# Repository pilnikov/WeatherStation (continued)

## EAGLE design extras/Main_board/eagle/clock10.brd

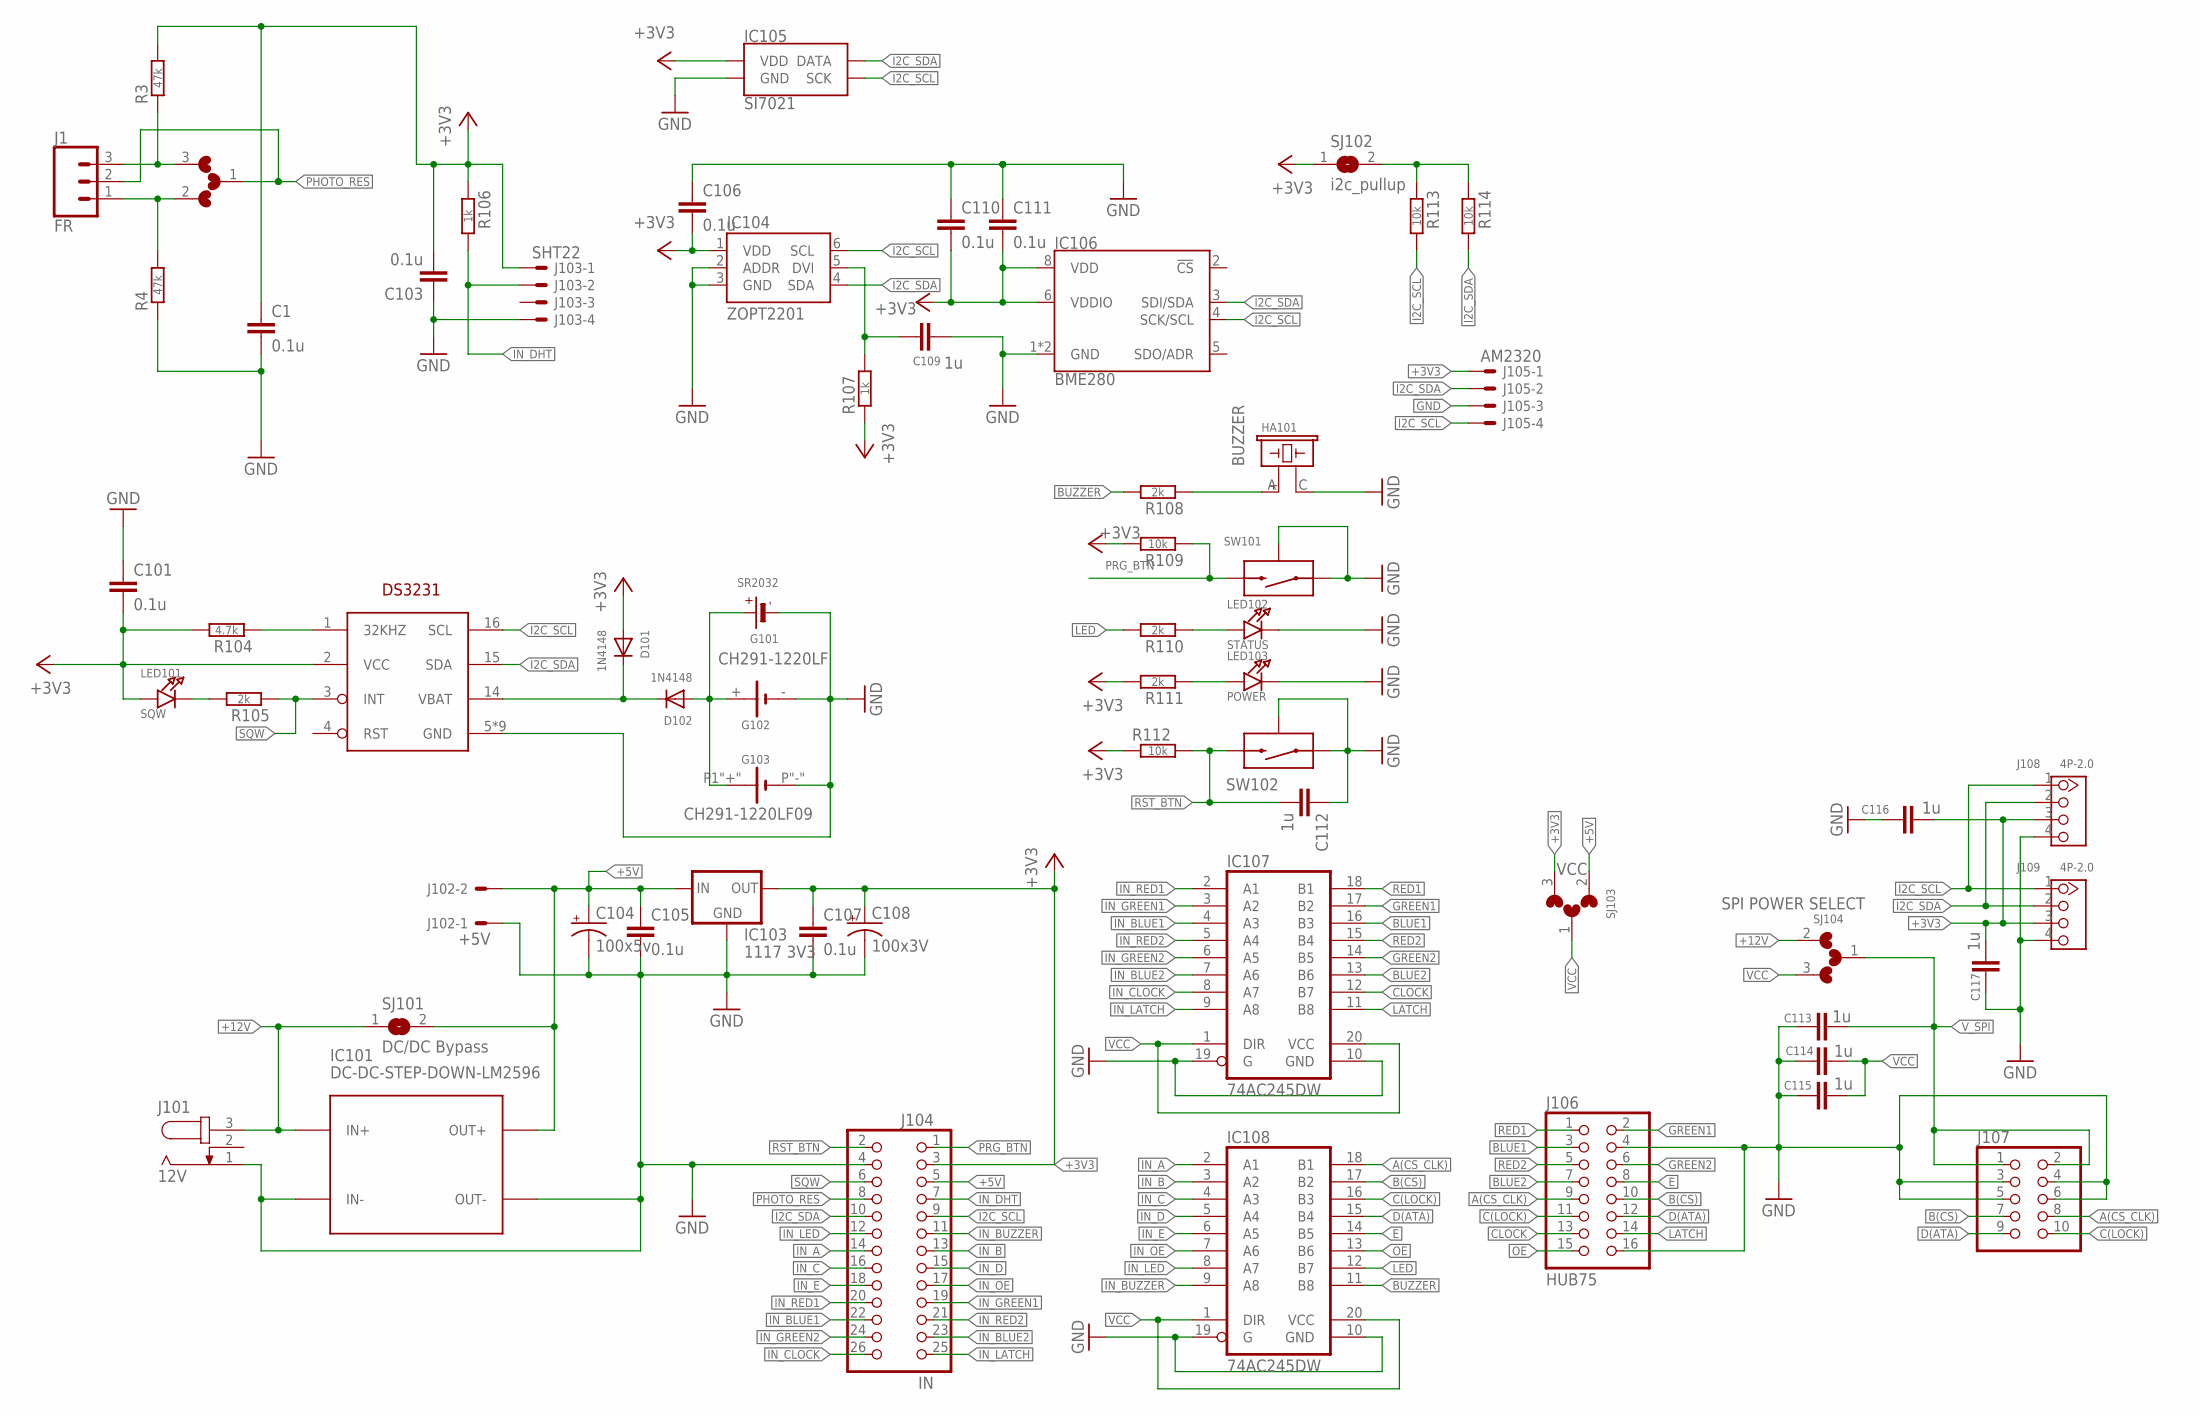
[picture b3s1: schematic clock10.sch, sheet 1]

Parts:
C1, C101, C103, C105, C106, C107, C110, C111: 0.1u; 0603-CAP
C104: 100x5v; CPOL-RADIAL-100UF-25V
C108: 100x3V; CPOL-RADIAL-100UF-25V
C109, C112, C113, C114, C115, C116, C117: 1u; 0603-CAP
D101, D102: 1N4148; SOD-323F
G101: SR2032; CR2032
G102: CH291-1220LF
G103: CH291-1220LF09; CH23-09LF
HA101: BUZZER; PBUZ_12X7.5
IC101: DC-DC-STEP-DOWN-LM2596
IC102: DS3231W; SO16W
IC103: 1117 3V3; SOT223
IC104: ZOPT2201; WSOF6L
IC105: SI7021; DFN-6-3X3-SI7021
IC106: BME280; LGA-8-2.5X2.5
IC107, IC108: 74AC245DW; SO20W
J1: FR; 1X03
J101: 12V; SPC4077
J102: +5V; 70543-02
J103: SHT22; 70543-04
J104: IN; 2X13
J105: AM2320; 70543-04
J106: HUB75; 2X08
J107: HEADER-2X5IDC; 2X05_IDC
J108, J109: 4P-2.0; HW4-2.0
LED101: SQW; CHIPLED_0603
LED102: STATUS; CHIPLED_0603
LED103: POWER; CHIPLED_0603
R3, R4: 47k; R0603
R104: 4.7k; R0603
R105, R108, R110, R111: 2k; R0603
R106, R107: 1k; R0603
R109, R112, R113, R114: 10k; R0603
SJ1: PR POS/NEG; MICROBUILDER_SOLDERJUMPER_ARROW_NOPASTE_3
SJ101: DC/DC Bypass; MICROBUILDER_SOLDERJUMPER_ARROW_NOPASTE
SJ102: i2c_pullup; MICROBUILDER_SOLDERJUMPER_ARROW_NOPASTE
SJ103: VCC; MICROBUILDER_SOLDERJUMPER_ARROW_NOPASTE_3
SJ104: SPI POWER SELECT; MICROBUILDER_SOLDERJUMPER_ARROW_NOPASTE_3
SW101: PRG; MICROPUSH-BUT_TOP
SW102: RST; MICROPUSH-BUT_TOP

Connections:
+3V3: C1.1, C101.2, C103.2, C106.2, C107.1, C108.1 (+), C110.2, C111.2, C116.2, C117.2, D101.A, IC102.2 (VCC), IC103.2 (OUT), IC103.4 (OUT), IC104.1 (VDD), IC105.VDD, IC106.6 (VDDIO), IC106.8 (VDD), J103.1, J104.3, J105.1, J108.3, J109.3, LED101.A, R3.2, R104.2, R106.1, R107.1, R109.2, R111.2, R112.1, SJ102.1, SJ103.3
+5V: C104.1 (+), C105.1, IC101.OUT+, IC103.3 (IN), J102.2, J104.5, SJ101.2, SJ103.2
+12V: IC101.IN+, J101.3, SJ101.1, SJ104.2
A(CS_CLK): IC108.18 (B1), J106.9, J107.8
B(CS): IC108.17 (B2), J106.10, J107.7
BLUE1: IC107.16 (B3), J106.3
BLUE2: IC107.13 (B6), J106.7
BUZ: HA101.A, R108.1
BUZZER: IC108.11 (B8), R108.2
C(LOCK): IC108.16 (B3), J106.11, J107.10
CLOCK: IC107.12 (B7), J106.13
D(ATA): IC108.15 (B4), J106.12, J107.9
E: IC108.14 (B5), J106.8
GND: C1.2, C101.1, C103.1, C104.2 (-), C105.2, C106.1, C107.2, C108.2 (-), C109.2, C110.1, C111.1, C112.1, C113.2, C114.2, C115.2, C116.1, C117.1, G101.-, G102.-, G103.P"-" (-), HA101.C, IC101.IN-, IC101.OUT-, IC102.5 (GND), IC102.6 (GND), IC102.7 (GND), IC102.8 (GND), IC102.9 (GND), IC102.10 (GND), IC102.11 (GND), IC102.12 (GND), IC102.13 (GND), IC103.1 (GND), IC104.2 (ADDR), IC104.3 (GND), IC105.GND, IC106.1 (GND), IC106.7 (GND), IC107.10 (GND), IC107.19 (G), IC108.10 (GND), IC108.19 (G), J101.1, J102.1, J103.4, J104.4, J105.3, J106.4, J106.16, J107.3, J107.4, J107.5, J107.6, J108.4, J109.4, LED102.C, LED103.C, R4.1, SW101.A, SW101.SH0 (SH), SW102.A, SW102.SH0 (SH); also elsewhere on the board
GREEN1: IC107.17 (B2), J106.2
GREEN2: IC107.14 (B5), J106.6
I2C_SCL: IC102.16 (SCL), IC104.6 (SCL), IC105.SCK, IC106.4 (SCK/SCL), J104.9, J105.4, J108.1, J109.1, R113.2
I2C_SDA: IC102.15 (SDA), IC104.4 (SDA), IC105.DATA, IC106.3 (SDI/SDA), J104.10, J105.2, J108.2, J109.2, R114.2
IN_A: IC108.2 (A1), J104.14
IN_B: IC108.3 (A2), J104.13
IN_BLUE1: IC107.4 (A3), J104.22
IN_BLUE2: IC107.7 (A6), J104.23
IN_BUZZER: IC108.9 (A8), J104.11
IN_C: IC108.4 (A3), J104.16
IN_CLOCK: IC107.8 (A7), J104.26
IN_D: IC108.5 (A4), J104.15
IN_DHT: J103.2, J104.7, R106.2
IN_E: IC108.6 (A5), J104.18
IN_GREEN1: IC107.3 (A2), J104.19
IN_GREEN2: IC107.6 (A5), J104.24
IN_LATCH: IC107.9 (A8), J104.25
IN_LED: IC108.8 (A7), J104.12
IN_OE: IC108.7 (A6), J104.17
IN_RED1: IC107.2 (A1), J104.20
IN_RED2: IC107.5 (A4), J104.21
LATCH: IC107.11 (B8), J106.14
LED: IC108.12 (B7), R110.2
unnamed: D101.C, D102.C, IC102.14 (VBAT)
unnamed: LED103.A, R111.1
unnamed: J1.3, R3.1, SJ1.3
unnamed: LED102.A, R110.1
unnamed: LED101.C, R105.2
unnamed: J1.1, R4.2, SJ1.2
unnamed: C109.1, IC104.5 (DVI), R107.2
unnamed: IC102.1 (32KHZ), R104.1
unnamed: R113.1, R114.1, SJ102.2
unnamed: D102.A, G101.+, G102.+, G103.P1"+" (+)
OE: IC108.13 (B6), J106.15
PHOTO_RES: J1.2, J104.8, SJ1.1
PRG_BTN: J104.1, R109.1, SW101.B
RED1: IC107.18 (B1), J106.1
RED2: IC107.15 (B4), J106.5
RST_BTN: C112.2, J104.2, R112.2, SW102.B
SQW: IC102.3 (INT), J104.6, R105.1
VCC: C114.1, C115.1, IC107.1 (DIR), IC107.20 (VCC), IC108.1 (DIR), IC108.20 (VCC), SJ103.1, SJ104.3
V_SPI: C113.1, J107.1, J107.2, SJ104.1

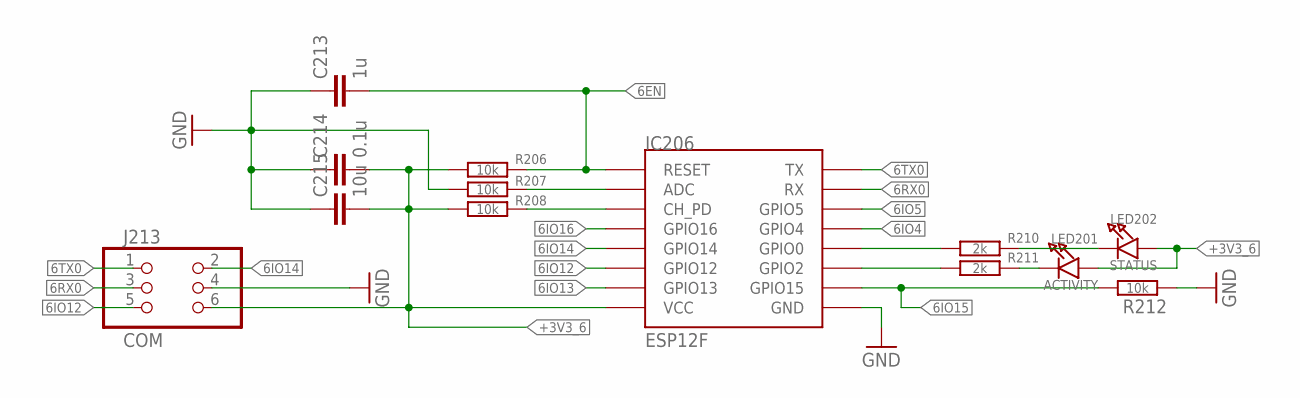
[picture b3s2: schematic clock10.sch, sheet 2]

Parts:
C213: 1u; 0603-CAP
C214: 0.1u; 0603-CAP
C215: 10u; 0603-CAP
IC206: ESP12F; ESP12-SMD
J213: COM; 2X03_SMT
LED201: ACTIVITY; CHIPLED_0603
LED202: STATUS; CHIPLED_0603
R206, R207, R208, R212: 10k; R0603
R210, R211: 2k; R0603

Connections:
6EN: C213.2, IC206.RESET, R206.1
6IO0: IC206.GPIO0, R210.1
6IO2: IC206.GPIO2, R211.1
6IO4: IC206.GPIO4
6IO5: IC206.GPIO5
6IO12: IC206.GPIO12, J213.5
6IO13: IC206.GPIO13
6IO14: IC206.GPIO14, J213.2
6IO15: IC206.GPIO15, R212.2
6IO16: IC206.GPIO16
6RX0: IC206.RXD0 (RX), J213.3
6TX0: IC206.TXD0 (TX), J213.1
+3V3_6: C214.2, C215.2, IC206.VCC, J213.6, LED201.A, LED202.A, R206.2, R208.2
GND: C213.1, C214.1, C215.1, IC206.GND, J213.4, R207.2, R212.1; also elsewhere on the board
unnamed: IC206.CH_PD, R208.1
unnamed: IC206.ADC, R207.1
unnamed: LED202.C, R210.2
unnamed: LED201.C, R211.2

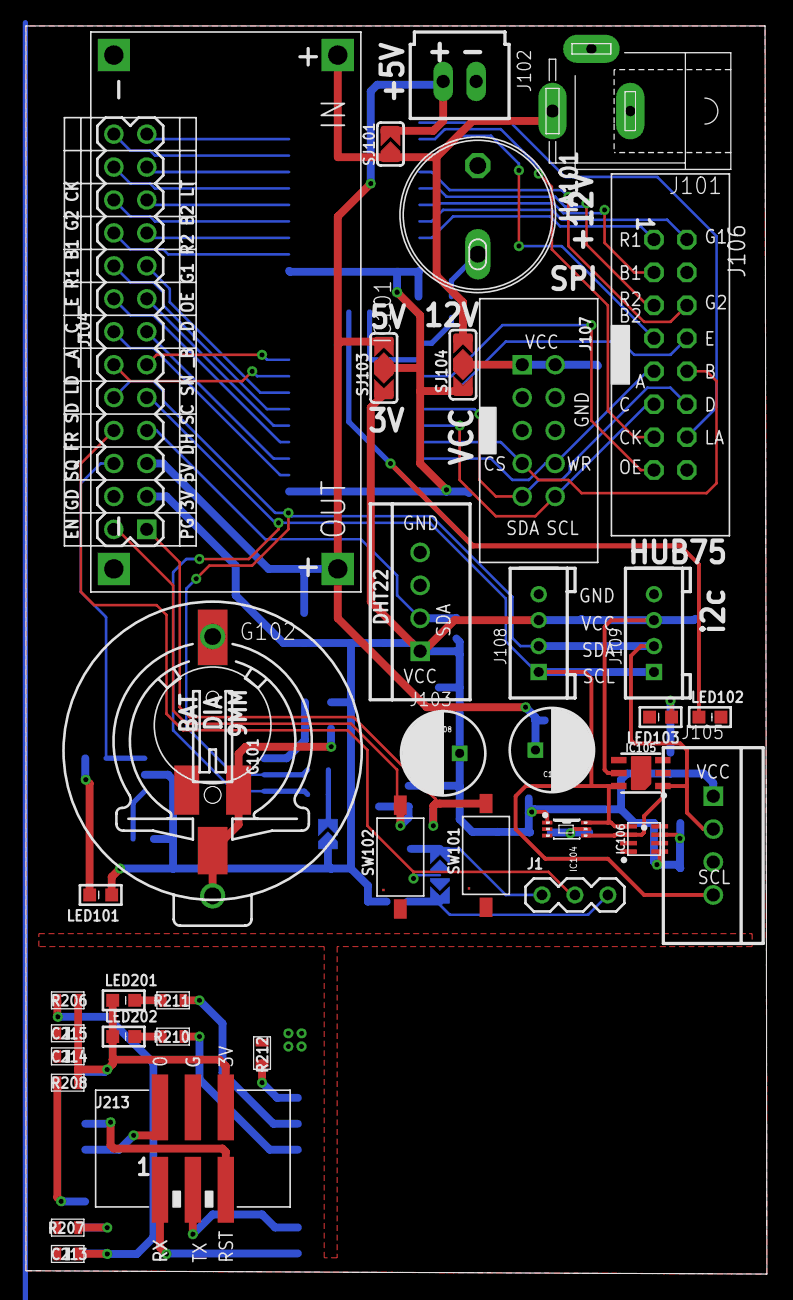
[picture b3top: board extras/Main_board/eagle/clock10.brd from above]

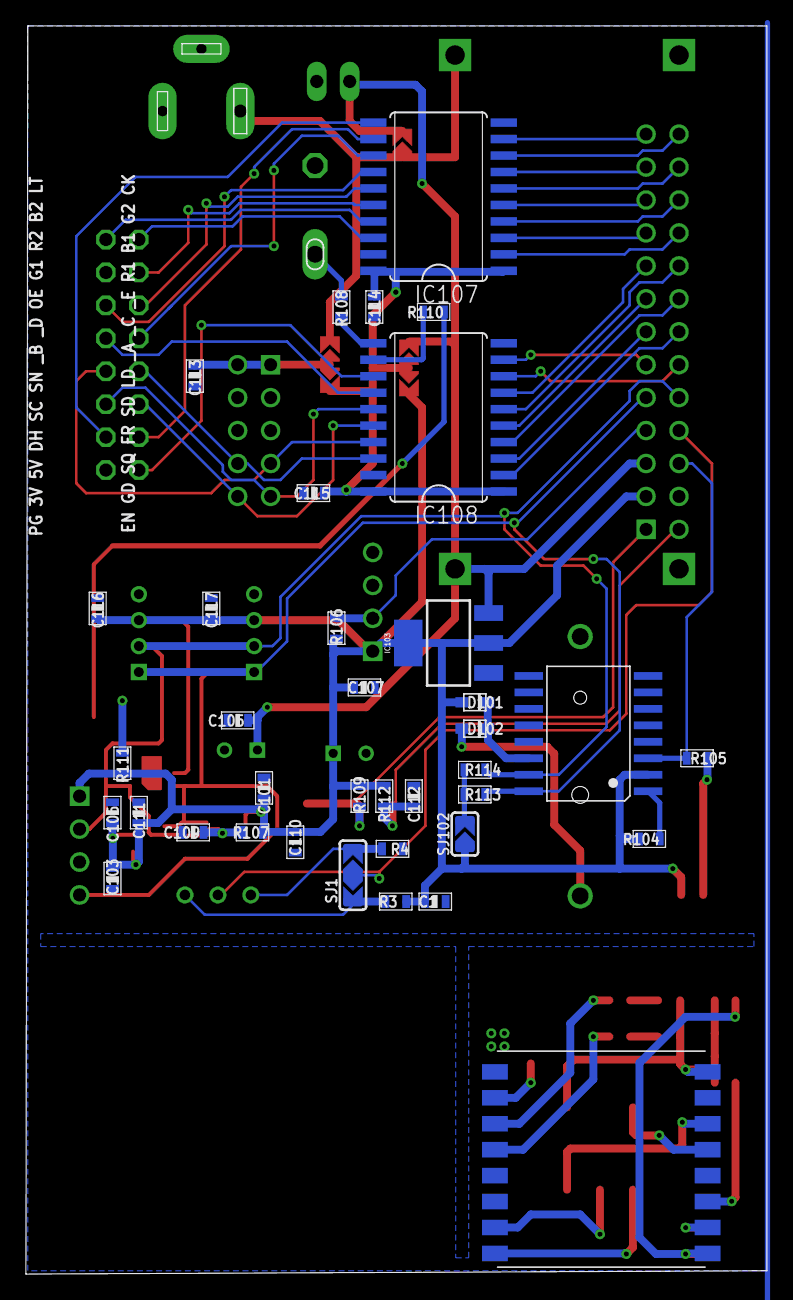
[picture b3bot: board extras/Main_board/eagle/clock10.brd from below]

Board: 2 copper layers, 57.1 x 96.3 mm, 77 parts (37 on the bottom side), 69 nets.

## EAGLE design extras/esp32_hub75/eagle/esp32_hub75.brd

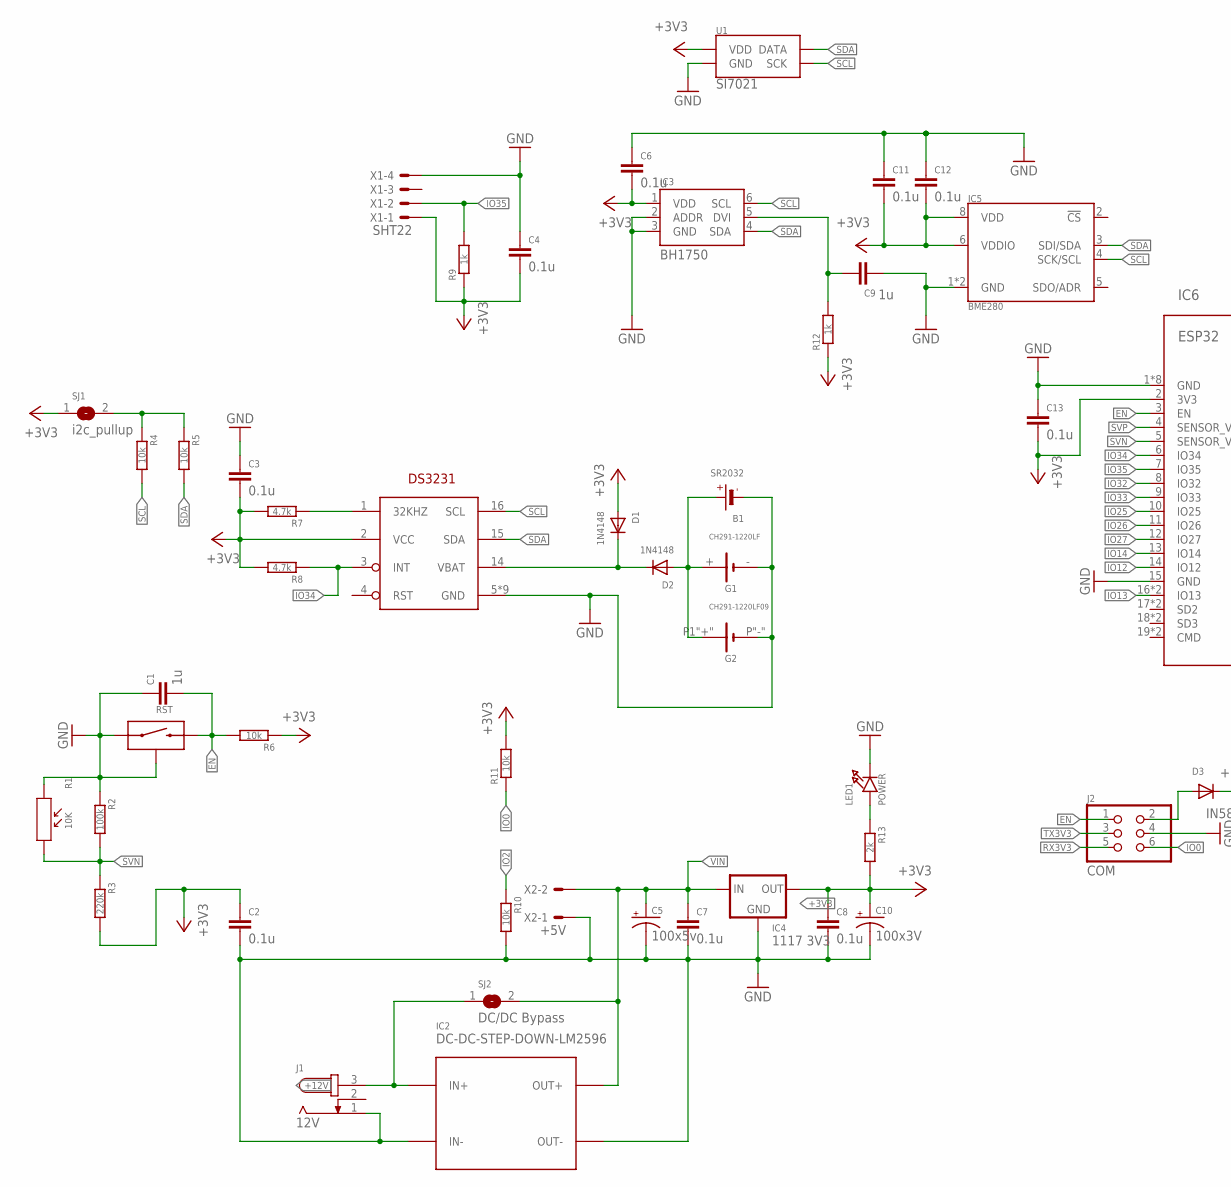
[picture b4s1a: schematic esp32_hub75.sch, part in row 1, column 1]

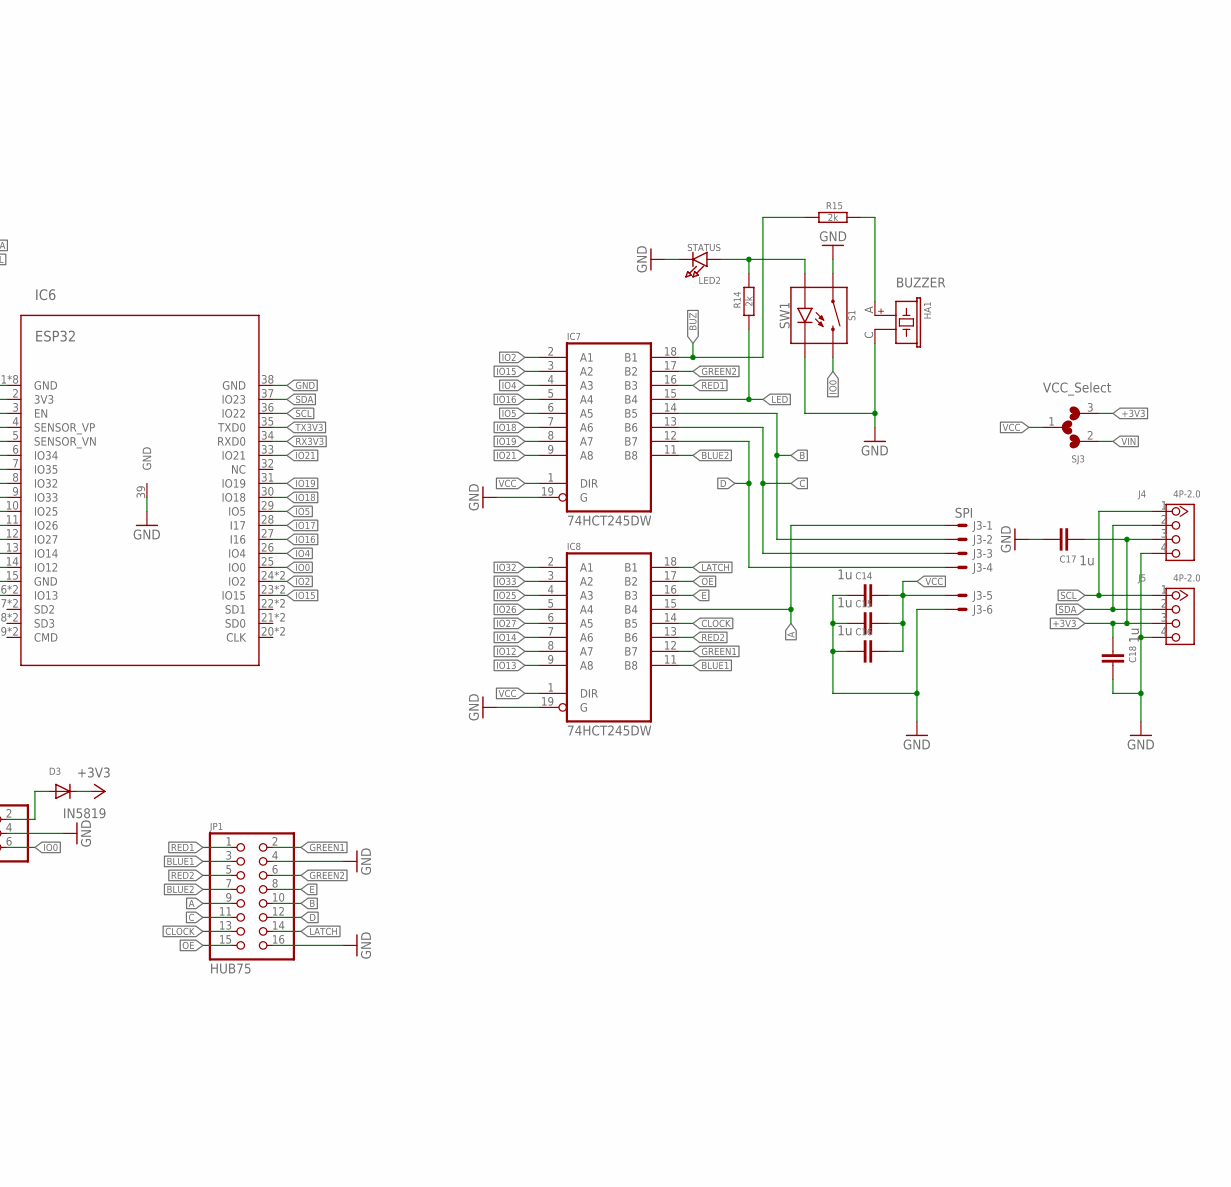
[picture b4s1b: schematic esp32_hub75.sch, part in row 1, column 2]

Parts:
B1: SR2032; CR2032
C1, C9, C14, C15, C16, C17, C18: 1u; 0603-CAP
C2, C3, C4, C6, C7, C8, C11, C12, C13: 0.1u; 0603-CAP
C5: 100x5v; CPOL-RADIAL-100UF-25V
C10: 100x3V; CPOL-RADIAL-100UF-25V
D1, D2: 1N4148; SOD-323F
D3: IN5819; SOD123
G1: CH291-1220LF
G2: CH291-1220LF09; CH23-09LF
HA1: BUZZER; PBUZ_12X7.5
IC1: DS3231W; SO16W
IC2: DC-DC-STEP-DOWN-LM2596
IC3: BH1750; WSOF6L
IC4: 1117 3V3; SOT223
IC5: BME280; LGA-8-2.5X2.5
IC6: ESP32; ESP32-WROOVER/WROOM
IC7, IC8: 74HCT245DW; SO20W
J1: 12V; SPC4077
J2: COM; 2X03
J3: SPI; 70543-06
J4, J5: 4P-2.0; HW4-2.0
JP1: HUB75; 2X08
LED1: POWER; CHIPLED_0603
LED2: STATUS; CHIPLED_0603
R1: 10K; SNR2-3.0
R2: 100k; R0603
R3: 220k; R0603
R4, R5, R6, R10, R11: 10k; R0603
R7, R8: 4.7k; R0603
R9, R12: 1k; R0603
R13, R14, R15: 2k; R0603
RST: RST; MICROPUSH-BUT_TOP
S1: SW1; TACTILE_SWITCH_LED_PTH_12MM_KIT
SJ1: i2c_pullup; MICROBUILDER_SOLDERJUMPER_ARROW_NOPASTE
SJ2: DC/DC Bypass; MICROBUILDER_SOLDERJUMPER_ARROW_NOPASTE
SJ3: VCC_Select; MICROBUILDER_SOLDERJUMPER_ARROW_NOPASTE_3
U1: SI7021; DFN-6-3X3-SI7021
X1: SHT22; 70543-04
X2: +5V; 70543-02

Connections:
+3V3: C2.1, C3.2, C4.2, C6.2, C8.1, C10.1 (+), C11.2, C12.2, C13.2, C17.2, C18.2, D1.A, D3.C, IC1.2 (VCC), IC3.1 (VDD), IC4.2 (OUT), IC4.4 (OUT), IC5.6 (VDDIO), IC5.8 (VDD), IC6.2 (3V3), J4.3, J5.3, R3.2, R6.1, R7.2, R8.2, R9.1, R11.2, R12.1, R13.2, SJ1.1, SJ3.3, U1.VDD, X1.1
+12V: IC2.IN+, J1.3, SJ2.1
A: IC8.15 (B4), J3.1, JP1.9
B: IC7.14 (B5), J3.2, JP1.10
BLUE1: IC8.11 (B8), JP1.3
BLUE2: IC7.11 (B8), JP1.7
BUZ: HA1.A, R15.1
C: IC7.13 (B6), J3.3, JP1.11
CLOCK: IC8.14 (B5), JP1.13
D: IC7.12 (B7), J3.4, JP1.12
E: IC8.16 (B3), JP1.8
EN: C1.2, IC6.3 (EN), J2.1, R6.2, RST.B
GND: B1.-, C1.1, C2.2, C3.1, C4.1, C5.2 (-), C6.1, C7.2, C8.2, C9.2, C10.2 (-), C11.1, C12.1, C13.1, C14.2, C15.2, C16.2, C17.1, C18.1, G1.-, G2.P"-" (-), HA1.C, IC1.5 (GND), IC1.6 (GND), IC1.7 (GND), IC1.8 (GND), IC1.9 (GND), IC1.10 (GND), IC1.11 (GND), IC1.12 (GND), IC1.13 (GND), IC2.IN-, IC2.OUT-, IC3.2 (ADDR), IC3.3 (GND), IC4.1 (GND), IC5.1 (GND), IC5.7 (GND), IC6.1 (GND), IC6.15 (GND), IC6.38 (GND), IC6.39 (GND), IC6.GND, IC6.PAD$1 (GND), IC6.PAD$4 (GND), IC6.PAD$5 (GND), IC6.PAD$7 (GND), IC6.PAD$8 (GND), IC6.PAD$9 (GND), IC7.10 (GND), IC7.19 (G), IC8.10 (GND), IC8.19 (G), J1.1, J2.4, J3.6, J4.4, J5.4, JP1.4, JP1.16, LED1.C, LED2.C, R1.1, R2.1, R10.2, RST.A, RST.SH0 (SH), S1.3 (1), S1.4 (1), S1.C, U1.GND, X1.4, X2.1
GREEN1: IC8.12 (B7), JP1.2
GREEN2: IC7.17 (B2), JP1.6
IO0: IC6.25 (IO0), J2.6, R11.1, S1.1 (2), S1.2
IO2: IC6.24 (IO2), IC6.48 (IO2), IC7.2 (A1), R10.1
IO4: IC6.26 (IO4), IC7.4 (A3)
IO5: IC6.29 (IO5), IC7.6 (A5)
IO12: IC6.14 (IO12), IC8.8 (A7)
IO13: IC6.16 (IO13), IC6.40 (IO13), IC8.9 (A8)
IO14: IC6.13 (IO14), IC8.7 (A6)
IO15: IC6.23 (IO15), IC6.47 (IO15), IC7.3 (A2)
IO16: IC6.27 (I16), IC7.5 (A4)
IO17: IC6.28 (I17)
IO18: IC6.30 (IO18), IC7.7 (A6)
IO19: IC6.31 (IO19), IC7.8 (A7)
IO21: IC6.33 (IO21), IC7.9 (A8)
IO25: IC6.10 (IO25), IC8.4 (A3)
IO26: IC6.11 (IO26), IC8.5 (A4)
IO27: IC6.12 (IO27), IC8.6 (A5)
IO32: IC6.8 (IO32), IC8.2 (A1)
IO33: IC6.9 (IO33), IC8.3 (A2)
IO34: IC1.3 (INT), IC6.6 (IO34), R8.1
IO35: IC6.7 (IO35), R9.2, X1.2
LATCH: IC8.18 (B1), JP1.14
LED: IC7.15 (B4), R14.2
unnamed: D1.C, D2.C, IC1.14 (VBAT)
unnamed: LED1.A, R13.1
unnamed: LED2.A, R14.1, S1.A
unnamed: C9.1, IC3.5 (DVI), R12.2
unnamed: IC1.1 (32KHZ), R7.1
unnamed: R4.1, R5.1, SJ1.2
unnamed: D3.A, J2.2
unnamed: B1.+, D2.A, G1.+, G2.P1"+" (+)
OE: IC8.17 (B2), JP1.15
RED1: IC7.16 (B3), JP1.1
RED2: IC8.13 (B6), JP1.5
RX3V3: IC6.34 (RXD0), J2.5
SCL: IC1.16 (SCL), IC3.6 (SCL), IC5.4 (SCK/SCL), IC6.36 (IO22), J4.1, J5.1, R4.2, U1.SCK
SDA: IC1.15 (SDA), IC3.4 (SDA), IC5.3 (SDI/SDA), IC6.37 (IO23), J4.2, J5.2, R5.2, U1.DATA
SVN: IC6.5 (SENSOR_VN), R1.2, R2.2, R3.1
SVP: IC6.4 (SENSOR_VP)
TX3V3: IC6.35 (TXD0), J2.3
VCC: C14.1, C15.1, C16.1, IC7.1 (DIR), IC7.20 (VCC), IC8.1 (DIR), IC8.20 (VCC), J3.5, SJ3.1
VIN: C5.1 (+), C7.1, IC2.OUT+, IC4.3 (IN), SJ2.2, SJ3.2, X2.2
_BUZ: IC7.18 (B1), R15.2

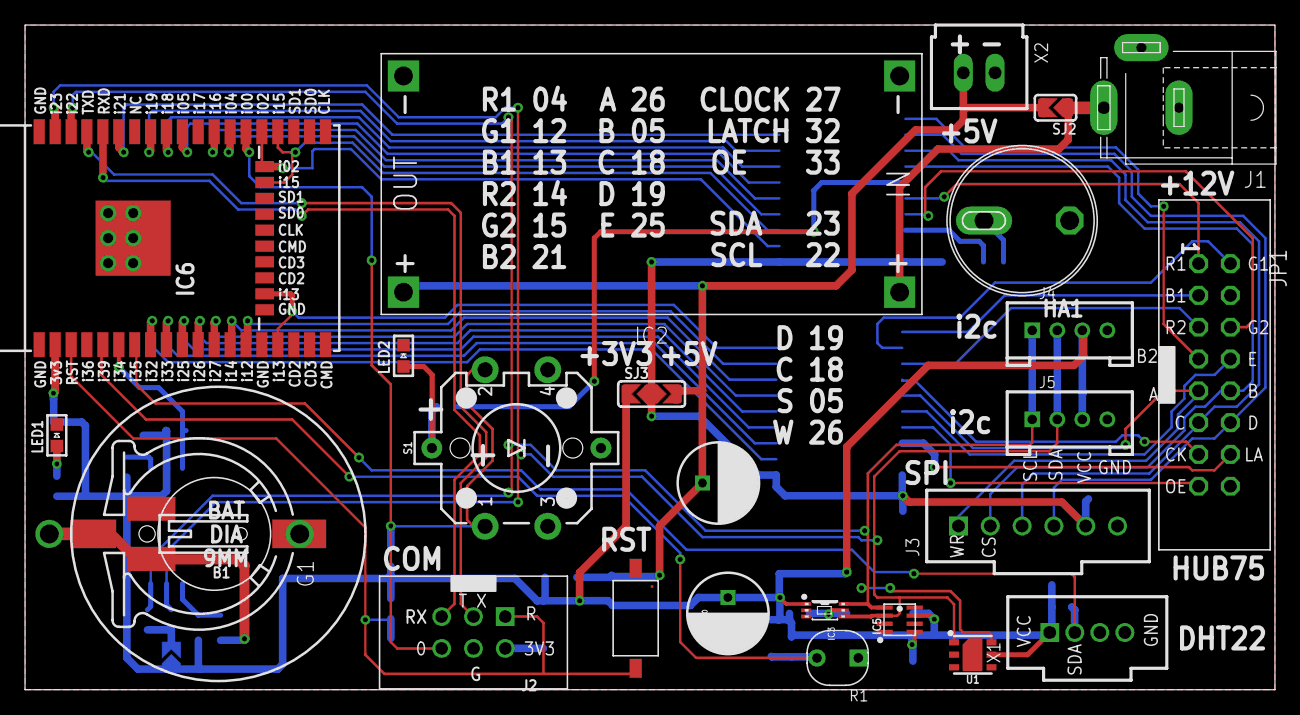
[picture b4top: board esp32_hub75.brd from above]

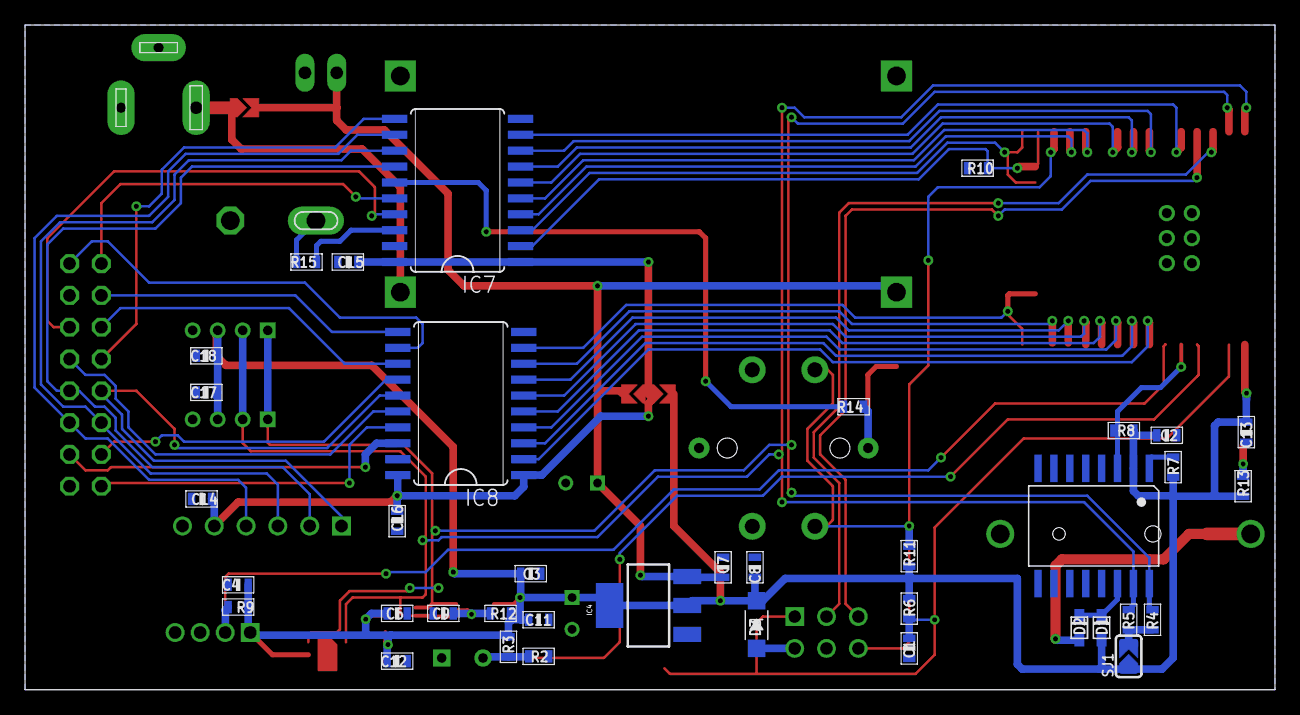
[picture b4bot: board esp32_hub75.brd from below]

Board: 2 copper layers, 99.8 x 53.1 mm, 64 parts (38 on the bottom side), 55 nets.

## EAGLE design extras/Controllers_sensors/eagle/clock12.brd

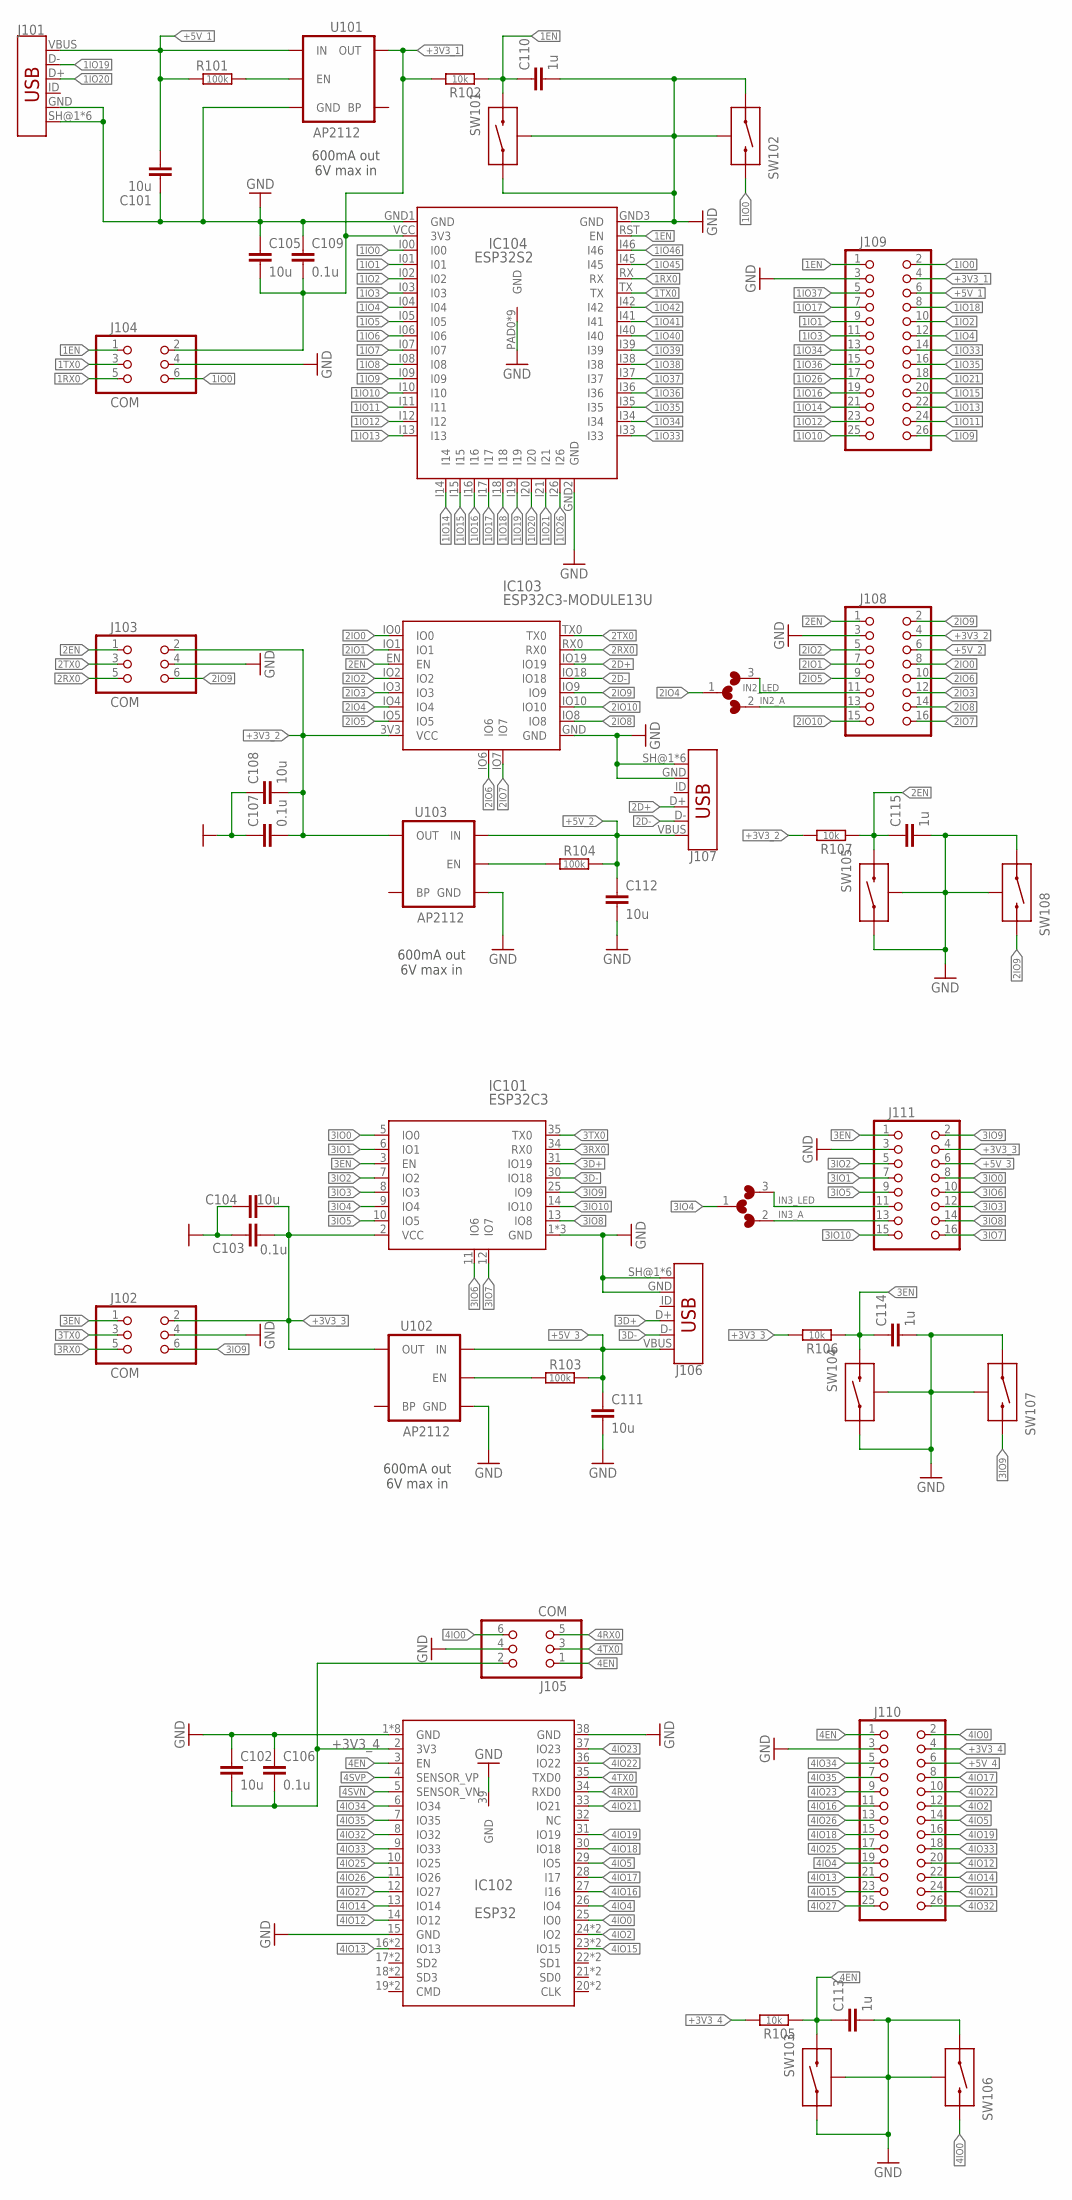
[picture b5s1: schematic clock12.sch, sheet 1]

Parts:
C101, C102, C104, C105, C108, C111, C112: 10u; 0603-CAP
C103, C106, C107, C109: 0.1u; 0603-CAP
C110, C113, C114, C115: 1u; 0603-CAP
IC101: ESP32C3; ESP32C3-S
IC102: ESP32; ESP32-WROOVER/WROOM
IC103: ESP32C3-MODULE13U; ESP32C3-13U
IC104: ESP32S2; ESP-12K
J101, J106, J107: USB_MICRO-BFEMALE_SMT_; USB-B-MICRO-SMD_MY
J102, J103, J104, J105: COM; 2X03_SMT
J108, J111: HEADER-2X8; 2X8
J109, J110: HEADER-2X13; 2X13
R101, R103, R104: 100k; R0603
R102, R105, R106, R107: 10k; R0603
SJ101, SJ102: L/W; MICROBUILDER_SOLDERJUMPER_ARROW_NOPASTE_3
SW101, SW103, SW104, SW105: RST; MICROPUSH-BUT_TOP
SW102, SW106, SW107, SW108: PRG; MICROPUSH-BUT_TOP
U101, U102, U103: AP2112; SOT23-5

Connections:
1EN: C110.1, IC104.RST (EN), J104.1, J109.1, R102.1, SW101.B
1EN_P: R101.2, U101.3 (EN)
1IO0: IC104.I00, J104.6, J109.2, SW102.B
1IO1: IC104.I01, J109.9
1IO2: IC104.I02, J109.10
1IO3: IC104.I03, J109.11
1IO4: IC104.I04, J109.12
1IO5: IC104.I05
1IO6: IC104.I06
1IO7: IC104.I07
1IO8: IC104.I08
1IO9: IC104.I09, J109.26
1IO10: IC104.I10, J109.25
1IO11: IC104.I11, J109.24
1IO12: IC104.I12, J109.23
1IO13: IC104.I13, J109.22
1IO14: IC104.I14, J109.21
1IO15: IC104.I15, J109.20
1IO16: IC104.I16, J109.19
1IO17: IC104.I17, J109.7
1IO18: IC104.I18, J109.8
1IO19: IC104.I19, J101.D-
1IO20: IC104.I20, J101.D+
1IO21: IC104.I21, J109.18
1IO26: IC104.I26, J109.17
1IO33: IC104.I33, J109.14
1IO34: IC104.I34, J109.13
1IO35: IC104.I35, J109.16
1IO36: IC104.I36, J109.15
1IO37: IC104.I37, J109.5
1IO38: IC104.I38
1IO39: IC104.I39
1IO40: IC104.I40
1IO41: IC104.I41
1IO42: IC104.I42
1IO45: IC104.I45
1IO46: IC104.I46
1RX0: IC104.RX, J104.5
1TX0: IC104.TX, J104.3
2D+: IC103.IO19, J107.D+
2D-: IC103.IO18, J107.D-
2EN: C115.1, IC103.EN, J103.1, J108.1, R107.1, SW105.B
2EN_P: R104.2, U103.3 (EN)
2IO0: IC103.IO0, J108.8
2IO1: IC103.IO1, J108.7
2IO2: IC103.IO2, J108.5
2IO3: IC103.IO3, J108.12
2IO4: IC103.IO4, SJ101.1
2IO5: IC103.IO5, J108.9
2IO6: IC103.IO6, J108.10
2IO7: IC103.IO7, J108.16
2IO8: IC103.IO8, J108.14
2IO9: IC103.IO9, J103.6, J108.2, SW108.B
2IO10: IC103.IO10, J108.15
2RX0: IC103.RX0, J103.5
2TX0: IC103.TX0, J103.3
3D+: IC101.31 (IO19), J106.D+
3D-: IC101.30 (IO18), J106.D-
3EN: C114.1, IC101.3 (EN), J102.1, J111.1, R106.1, SW104.B
3EN_P: R103.2, U102.3 (EN)
3IO0: IC101.5 (IO0), J111.8
3IO1: IC101.6 (IO1), J111.7
3IO2: IC101.7 (IO2), J111.5
3IO3: IC101.8 (IO3), J111.12
3IO4: IC101.9 (IO4), SJ102.1
3IO5: IC101.10 (IO5), J111.9
3IO6: IC101.11 (IO6), J111.10
3IO7: IC101.12 (IO7), J111.16
3IO8: IC101.13 (IO8), J111.14
3IO9: IC101.25 (IO9), J102.6, J111.2, SW107.B
3IO10: IC101.14 (IO10), J111.15
3RX0: IC101.34 (RX0), J102.5
3TX0: IC101.35 (TX0), J102.3
4EN: C113.1, IC102.3 (EN), J105.1, J110.1, R105.1, SW103.B
4IO0: IC102.25 (IO0), J105.6, J110.2, SW106.B
4IO2: IC102.24 (IO2), IC102.48 (IO2), J110.12
4IO4: IC102.26 (IO4), J110.19
4IO5: IC102.29 (IO5), J110.14
4IO12: IC102.14 (IO12), J110.20
4IO13: IC102.16 (IO13), IC102.40 (IO13), J110.21
4IO14: IC102.13 (IO14), J110.22
4IO15: IC102.23 (IO15), IC102.47 (IO15), J110.23
4IO16: IC102.27 (I16), J110.11
4IO17: IC102.28 (I17), J110.8
4IO18: IC102.30 (IO18), J110.15
4IO19: IC102.31 (IO19), J110.16
4IO21: IC102.33 (IO21), J110.24
4IO22: IC102.36 (IO22), J110.10
4IO23: IC102.37 (IO23), J110.9
4IO25: IC102.10 (IO25), J110.17
4IO26: IC102.11 (IO26), J110.13
4IO27: IC102.12 (IO27), J110.25
4IO32: IC102.8 (IO32), J110.26
4IO33: IC102.9 (IO33), J110.18
4IO34: IC102.6 (IO34), J110.5
4IO35: IC102.7 (IO35), J110.7
4RX0: IC102.34 (RXD0), J105.5
4SVN: IC102.5 (SENSOR_VN)
4SVP: IC102.4 (SENSOR_VP)
4TX0: IC102.35 (TXD0), J105.3
+3V3_1: C105.2, C109.2, IC104.VCC (3V3), J104.2, J109.4, R102.2, U101.5 (OUT)
+3V3_2: C107.2, C108.2, IC103.3V3 (VCC), J103.2, J108.4, R107.2, U103.5 (OUT)
+3V3_3: C103.2, C104.2, IC101.2 (VCC), J102.2, J111.4, R106.2, U102.5 (OUT)
+3V3_4: C102.2, C106.2, IC102.2 (3V3), J105.2, J110.4, R105.2
+5V_1: C101.1, J101.VBUS, J109.6, R101.1, U101.1 (IN)
+5V_2: C112.1, J107.VBUS, J108.6, R104.1, U103.1 (IN)
+5V_3: C111.1, J106.VBUS, J111.6, R103.1, U102.1 (IN)
+5V_4: J110.6
GND: C101.2, C102.1, C103.1, C104.1, C105.1, C106.1, C107.1, C108.1, C109.1, C110.2, C111.2, C112.2, C113.2, C114.2, C115.2, IC101.1 (GND), IC101.38 (GND), IC101.39 (GND), IC102.1 (GND), IC102.15 (GND), IC102.38 (GND), IC102.39 (GND), IC102.GND, IC102.PAD$1 (GND), IC102.PAD$4 (GND), IC102.PAD$5 (GND), IC102.PAD$7 (GND), IC102.PAD$8 (GND), IC102.PAD$9 (GND), IC103.GND, IC104.GND1 (GND), IC104.GND2 (GND), IC104.GND3 (GND), IC104.PAD0 (GND), IC104.PAD1 (GND), IC104.PAD2 (GND), IC104.PAD3 (GND), IC104.PAD4 (GND), IC104.PAD5 (GND), IC104.PAD6 (GND), IC104.PAD7 (GND), IC104.PAD8 (GND), J101.GND, J101.SH@1 (SHIELD), J101.SH@2 (SHIELD), J101.SH@3 (SHIELD), J101.SH@4 (SHIELD), J101.SH@5 (SHIELD), J101.SH@6 (SHIELD), J102.4, J103.4, J104.4, J105.4, J106.GND, J106.SH@1 (SHIELD), J106.SH@2 (SHIELD), J106.SH@3 (SHIELD), J106.SH@4 (SHIELD), J106.SH@5 (SHIELD), J106.SH@6 (SHIELD), J107.GND, J107.SH@1 (SHIELD), J107.SH@2 (SHIELD), J107.SH@3 (SHIELD), J107.SH@4 (SHIELD), J107.SH@5 (SHIELD), J107.SH@6 (SHIELD), J108.3, J109.3, J110.3, J111.3, SW101.A, SW101.SH0 (SH), SW102.A, SW102.SH0 (SH), SW103.A, SW103.SH0 (SH), SW104.A, SW104.SH0 (SH), SW105.A, SW105.SH0 (SH), SW106.A, SW106.SH0 (SH), SW107.A, SW107.SH0 (SH), SW108.A, SW108.SH0 (SH), U101.2 (GND), U102.2 (GND), U103.2 (GND); also elsewhere on the board
IN2_A: J108.13, SJ101.2
IN2_LED: J108.11, SJ101.3
IN3_A: J111.13, SJ102.2
IN3_LED: J111.11, SJ102.3

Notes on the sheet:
600mA out 6V max in
